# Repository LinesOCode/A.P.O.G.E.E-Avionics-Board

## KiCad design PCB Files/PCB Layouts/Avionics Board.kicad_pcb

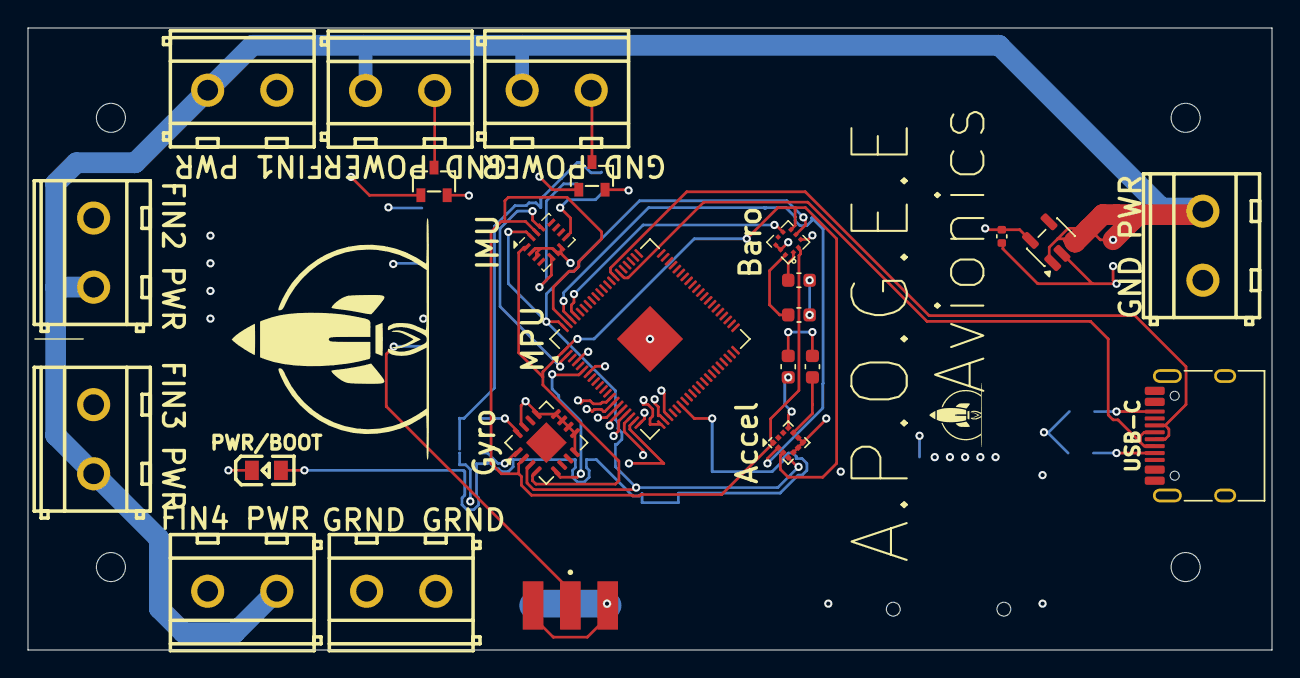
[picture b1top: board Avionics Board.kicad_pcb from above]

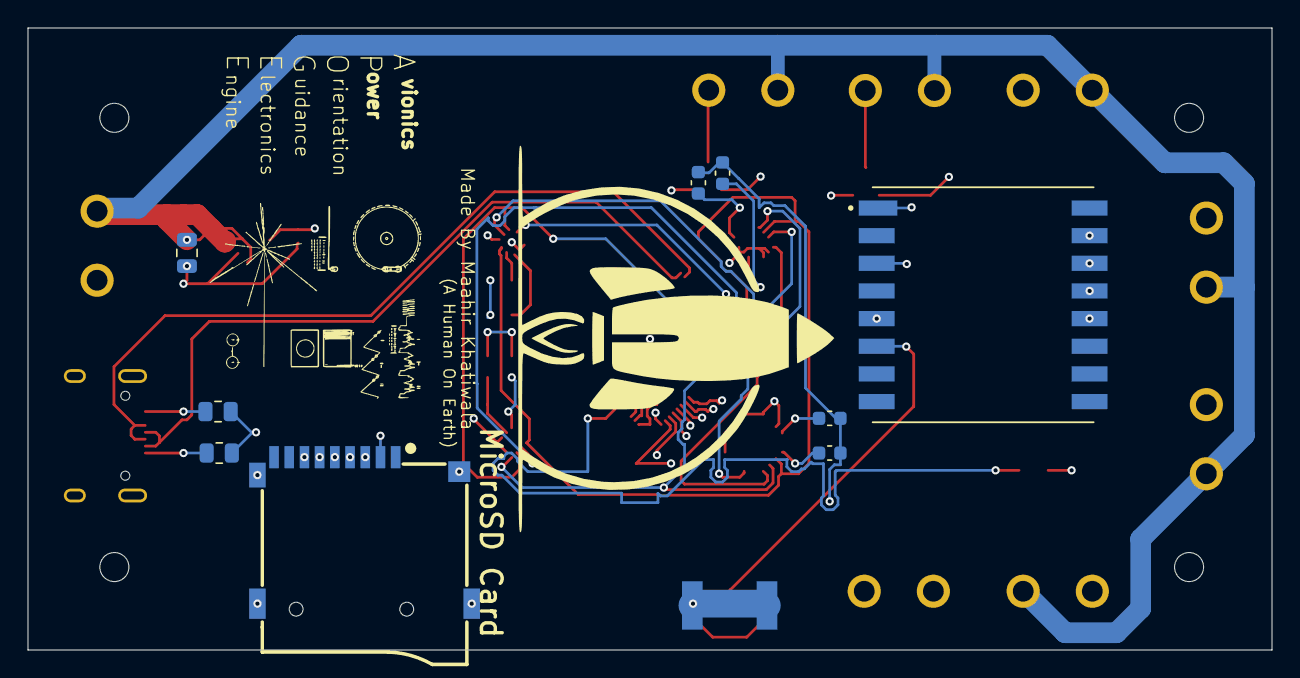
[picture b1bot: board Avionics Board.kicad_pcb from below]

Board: 4 copper layers, 90.0 x 45.0 mm, 29 parts (8 on the bottom side), 31 nets.

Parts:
Accel.1: LIS2DH12TR; LGA-12_2x2mm_P0.5mm
Baro1: SPL07-003
C1, C2, C3, C4, C5, C6, C7, C8: .1 uF; C_0603_1608Metric
C9: CL21A106KAYNNNE; C_0805_2012Metric
C10: CL05A105KO5NNNC; C_0402_1005Metric
Gyro1: A3G4250DTR; QFN-16-1EP_4x4mm_P0.65mm_EP2.1x2.1mm
IMU1: LIS2DH12TR-C; Bosch_LGA-14_3x2.5mm_P0.5mm
LED1: 0805G_Green
MPU1: Rasp Pi 2354B; QFN-80-1EP_10x10mm_P0.4mm_EP3.4x3.4mm
R1, R2: HRC0805F5101FNTN; R_0805_2012Metric
U2: Volt_Reg; SOT-23-5
U3, U4, U5, U6, U7, U8, U11, U12: DB127V-5_0-2P-BU-S
U9: JBL-102010052; Micro_SD_-_Avionics
USB-C: TYPE-C-31-M-12; USB_C_Receptacle_HRO_TYPE-C-31-M-12

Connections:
+3.3V: C1.2, C2.2, C3.2, C4.2, C5.2, C6.2, C7.2, C8.2, C10.1, MPU1.15 (IOVDD), U2.5 (VOUT), U9.4 (VDD)
+BATT: C9.2, U2.1 (VIN), U2.3 (EN), U3.2, U4.2, U5.2, U6.2, U8.2, U11.1, U12.2
CS_Accel: Accel.1.2 (CS), MPU1.78 (GPIO1)
CS_Baro: Baro1.6 (CSB), MPU1.77 (GPIO0)
CS_Gyro: Gyro1.5 (CS), MPU1.6 (GPIO8)
CS_IMU: IMU1.12 (CS), MPU1.2 (GPIO5)
DN-C: MPU1.66 (USB_DM), USB-C.A7 (DN1), USB-C.B7 (DN2)
DP-C: MPU1.67 (USB_DP), USB-C.A6 (DP1), USB-C.B6 (DP2)
GND: Accel.1.5 (RES), Accel.1.6 (GND), Accel.1.7 (GND), Accel.1.8 (GND), Baro1.3 (GND), Baro1.8 (GND), Baro1.9 (GND), C9.1, C10.2, Gyro1.8 (RES), Gyro1.9 (RES), Gyro1.10 (RES), Gyro1.11 (RES), Gyro1.12 (RES), Gyro1.13 (GND), Gyro1.15 (RES), IMU1.2 (SDx), IMU1.3 (SCx), IMU1.6 (GND), IMU1.7 (GND), LED1.2 (K), MPU1.81 (GND), R1.1, R2.1, U2.2 (GND), U7.1, U7.2, U9.6 (VSS), U9.9 (GND), U9.10 (GND), U9.11 (GND), U9.12 (GND), U11.2
unnamed: Accel.1.9 (VDD), C1.1
unnamed: Accel.1.10 (VDD_IO), C2.1
unnamed: Baro1.10 (VDD), C7.1
unnamed: Baro1.1 (VDDIO), C8.1
unnamed: C5.1, Gyro1.16 (Vdd)
unnamed: C6.1, Gyro1.1 (Vdd_IO)
unnamed: C3.1, IMU1.8 (VDD)
unnamed: C4.1, IMU1.5 (VDDIO)
unnamed: LED1.1 (A), MPU1.26 (GPIO25)
unnamed: R2.2, USB-C.A5 (CC1)
unnamed: R1.2, USB-C.B5 (CC2)
SD_CS: MPU1.17 (GPIO17), U9.2 (CD/DAT3)
SPI0_MISO: Accel.1.3 (SDO/SA0), Baro1.5 (SDO), Gyro1.4 (SDO/SA0), IMU1.1 (SDO/SA0), MPU1.1 (GPIO4)
SPI0_MOSI: Accel.1.4 (SDA/SDI/SDO), Baro1.4 (SDA), Gyro1.3 (SDA/SDI/SDO), IMU1.14 (SDA), MPU1.80 (GPIO3)
SPI0_SCK: Accel.1.1 (SCL/SPC), Baro1.2 (SCL), Gyro1.2 (SCL/SPC), IMU1.13 (SCL), MPU1.79 (GPIO2)
SPI1_MISO: MPU1.16 (GPIO16), U9.7 (DAT0)
SPI1_MOSI: MPU1.19 (GPIO19), U9.3 (CMD)
SPI1_SCK: MPU1.18 (GPIO18), U9.5 (CLK)
Serv_Sig_1: MPU1.20 (GPIO20), U3.1
Serv_Sig_2: MPU1.21 (GPIO21), U4.1
Serv_Sig_3: MPU1.22 (GPIO22), U5.1
Serv_Sig_4: MPU1.23 (GPIO23), U6.1

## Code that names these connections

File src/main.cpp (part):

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// Keep board wiring changes in this block.
// Sensor bus: configurable SPI pins (change these variables if you re-wire)
// Default mapping provided by user (GPIO numbers):
// SCK = GPIO2, MOSI = GPIO3, MISO = GPIO4
const uint8_t SENSOR_SPI_SCK_PIN = 2;
const uint8_t SENSOR_SPI_MOSI_PIN = 3;
const uint8_t SENSOR_SPI_MISO_PIN = 4;
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const uint8_t STORAGE_SPI_MISO_PIN = 16;
// Sensor chip-selects (changeable variables)
// Provided mapping from user:
// IMU CS GPIO5, Gyro CS GPIO8, Baro CS GPIO0, Accel CS GPIO1
const uint8_t IMU_SENSOR_CS = 5;   // ST LSM6DS3TR accelerometer + gyro
const uint8_t GYRO_SENSOR_CS = 8;  // ST A3G4250DTR gyro
const uint8_t BARO_SENSOR_CS = 0;  // Goertek SPL07-003 barometer
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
